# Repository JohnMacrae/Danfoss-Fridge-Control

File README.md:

# Danfoss-Fridge-Control

I have a Danfoss BD35 and BD50 compressor running the fridge and freezer on my boat. This project has been brewing since I sopke with a friend, Rick, back in 2016 but although I tinkered with it, I didn't get serious - mostly due to lack of confidence born out of lack of competence :)
While we were on board in 2019, however, the mechanical thermostat on the fridge (BD35) broke and I was forced to 'create' something out of what was on board  - an ESP8266, a DS18b20 and a chinesium relay.

It was successful and ran for months without any problems but as you can see it was a bit of a bodge.  So, I decided to make a board and run it on an ESP32.

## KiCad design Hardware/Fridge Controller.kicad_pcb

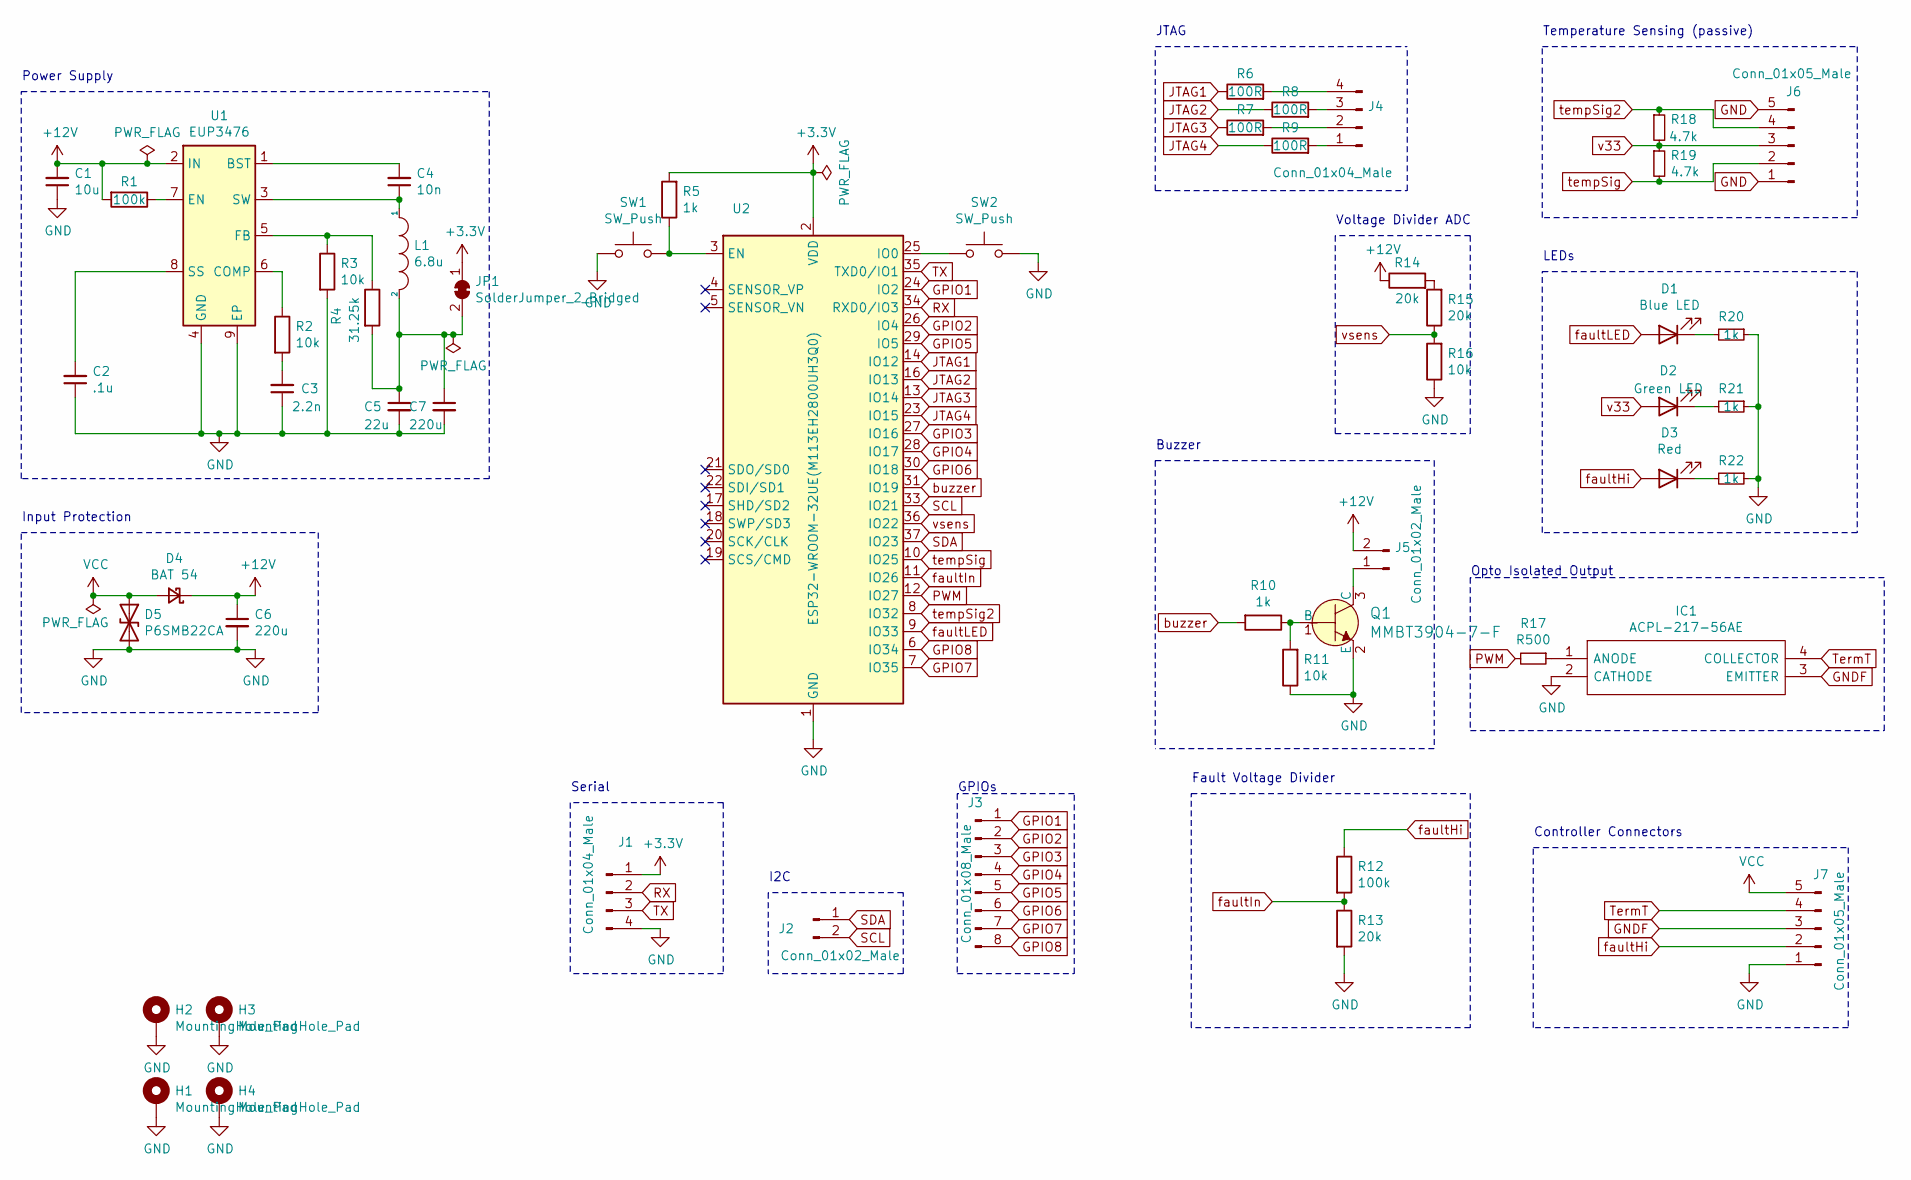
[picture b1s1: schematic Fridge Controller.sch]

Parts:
C1: 10u; C_0805_2012Metric_Pad1.15x1.40mm_HandSolder
C2: .1u; C_0805_2012Metric_Pad1.15x1.40mm_HandSolder
C3: 2.2n; C_0805_2012Metric_Pad1.15x1.40mm_HandSolder
C4: 10n; C_0805_2012Metric_Pad1.15x1.40mm_HandSolder
C5: 22u; C_0805_2012Metric_Pad1.15x1.40mm_HandSolder
C6: 220u; C_1206_3216Metric_Pad1.42x1.75mm_HandSolder
C7: 220u; CP_EIA-7343-31_Kemet-D_Pad2.25x2.55mm_HandSolder
D1: Blue LED; LED_1206_3216Metric
D2: Green LED; LED_1206_3216Metric
D3: Red; LED_1206_3216Metric
D4: BAT 54; D_SOT-23_ANK
D5: P6SMB22CA; D_SMB
H1, H2, H3, H4: MountingHole_Pad; MountingHole_3.2mm_M3_Pad_Via
IC1: ACPL-217-56AE; SOIC127P700X242-4N; Mouser Part Number 630-ACPL-217-56AE
J1, J4: Conn_01x04_Male; PinHeader_1x04_P2.54mm_Vertical
J2, J5: Conn_01x02_Male; PinHeader_1x02_P2.54mm_Vertical
J3: Conn_01x08_Male; PinHeader_1x08_P2.54mm_Vertical
J6, J7: Conn_01x05_Male; JST_XH_B5B-XH-A_1x05_P2.50mm_Vertical
JP1: SolderJumper_2_Bridged; SolderJumper-2_P1.3mm_Open_Pad1.0x1.5mm
L1: 6.8u; L_Abracon_ASPI-0630LR
Q1: MMBT3904-7-F; SOT-23-3; MPN MMBT3904-7-F; Digi-Key_PN MMBT3904-FDICT-ND
R1, R12: 100k; R_0805_2012Metric_Pad1.15x1.40mm_HandSolder
R2, R3, R11, R16: 10k; R_0805_2012Metric_Pad1.15x1.40mm_HandSolder
R4: 31.25k; R_0805_2012Metric_Pad1.15x1.40mm_HandSolder
R5, R10, R20, R21, R22: 1k; R_0805_2012Metric_Pad1.15x1.40mm_HandSolder
R6, R7, R8, R9: 100R; R_0805_2012Metric_Pad1.15x1.40mm_HandSolder
R13, R14, R15: 20k; R_0805_2012Metric_Pad1.15x1.40mm_HandSolder
R17: R500; R_0805_2012Metric_Pad1.15x1.40mm_HandSolder
R18, R19: 4.7k; R_0805_2012Metric_Pad1.15x1.40mm_HandSolder
SW1, SW2: SW_Push; SW_PUSH_6mm_H5mm
U1: EUP3476; HSOP-8-1EP_3.9x4.9mm_P1.27mm_EP2.41x3.1mm
U2: ESP32-WROOM-32UE(M113EH2800UH3Q0); ESP32-WROOM-32

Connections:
+3V3: J1.1, JP1.1 (A), R5.2, U2.2 (VDD)
+12V: C1.2, C6.1, D4.1 (K), J5.2, R1.2, R14.1, U1.2 (IN)
GND: C1.1, C2.1, C3.1, C5.2, C6.2, C7.2, D5.2 (A2), H1.1, H2.1, H3.1, H4.1, IC1.2 (CATHODE), J1.4, J6.1, J6.5, J7.1, Q1.2 (E), R3.2, R11.1, R13.2, R16.1, R20.1, R21.1, R22.1, SW1.1, SW2.2, U1.4 (GND), U1.9 (EP), U2.1 (GND), U2.15 (GND), U2.38 (GND), U2.39 (GND)
GNDF: IC1.3 (EMITTER), J7.3
GPIO1: J3.1, U2.24 (IO2)
GPIO2: J3.2, U2.26 (IO4)
GPIO3: J3.3, U2.27 (IO16)
GPIO4: J3.4, U2.28 (IO17)
GPIO5: J3.5, U2.29 (IO5)
GPIO6: J3.6, U2.30 (IO18)
GPIO7: J3.7, U2.7 (IO35)
GPIO8: J3.8, U2.6 (IO34)
JTAG1: R6.1, U2.14 (IO12)
JTAG2: R8.1, U2.16 (IO13)
JTAG3: R7.1, U2.13 (IO14)
JTAG4: R9.1, U2.23 (IO15)
unnamed: C2.2, U1.8 (SS)
unnamed: C3.2, R2.2
unnamed: C4.1, L1.1, U1.3 (SW)
unnamed: C4.2, U1.1 (BST)
unnamed: C5.1, C7.1, JP1.2 (B), L1.2, R4.2
unnamed: D1.1 (K), R20.2
unnamed: D2.1 (K), R21.2
unnamed: D3.1 (K), R22.2
unnamed: IC1.1 (ANODE), R17.1
unnamed: J4.1, R9.2
unnamed: J4.2, R7.2
unnamed: J4.3, R8.2
unnamed: J4.4, R6.2
unnamed: J5.1, Q1.3 (C)
unnamed: Q1.1 (B), R10.1, R11.2
unnamed: R1.1, U1.7 (EN)
unnamed: R2.1, U1.6 (COMP)
unnamed: R3.1, R4.1, U1.5 (FB)
unnamed: R5.1, SW1.2, U2.3 (EN)
unnamed: R14.2, R15.2
unnamed: SW2.1, U2.25 (IO0)
PWM: R17.2, U2.12 (IO27)
RX: J1.2, U2.34 (RXD0/IO3)
SCL: J2.2, U2.33 (IO21)
SDA: J2.1, U2.37 (IO23)
TX: J1.3, U2.35 (TXD0/IO1)
TermT: IC1.4 (COLLECTOR), J7.4
VCC: D4.2 (A), D5.1 (A1), J7.5
buzzer: R10.2, U2.31 (IO19)
faultHi: D3.2 (A), J7.2, R12.1
faultIn: R12.2, R13.1, U2.11 (IO26)
faultLED: D1.2 (A), U2.9 (IO33)
tempSig: J6.2, R19.2, U2.10 (IO25)
tempSig2: J6.4, R18.1, U2.8 (IO32)
v33: D2.2 (A), J6.3, R18.2, R19.1
vsens: R15.1, R16.2, U2.36 (IO22)

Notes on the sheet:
Temperature Sensing (passive)
LEDs
Opto Isolated Output
JTAG
Power Supply
Controller Connectors
Fault Voltage Divider
Buzzer
Voltage Divider ADC
GPIOs
Serial
I2C
Input Protection

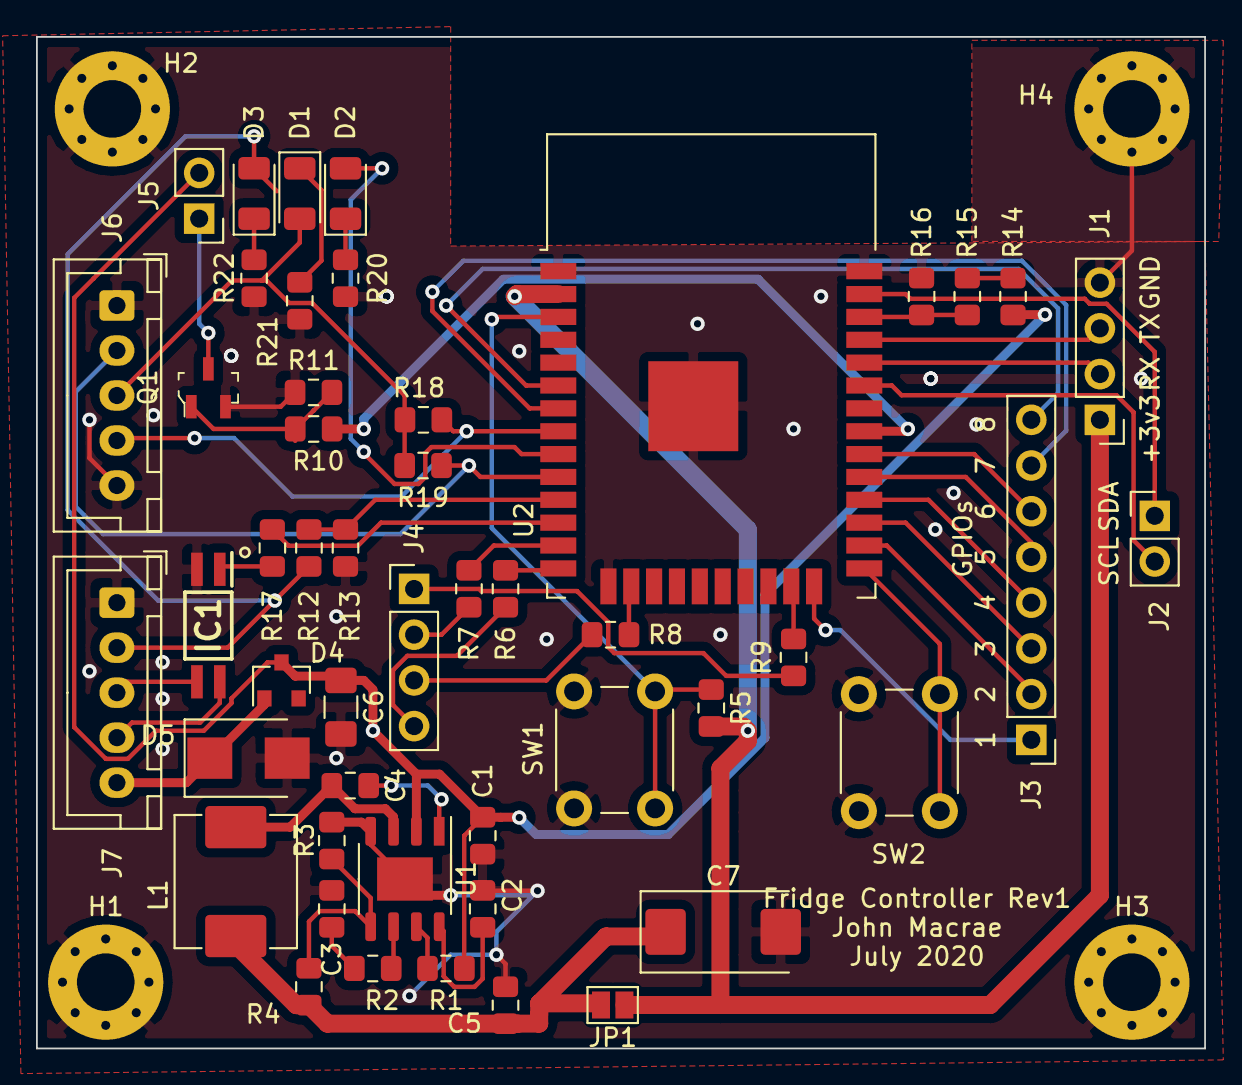
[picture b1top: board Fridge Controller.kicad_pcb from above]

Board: 2 copper layers, 64.9 x 56.2 mm, 53 parts (0 on the bottom side), 52 nets.

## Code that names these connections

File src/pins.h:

#include <Arduino.h>

#define TEMPSIG 21
#define GPIO2 2
#define TX 1
#define RX 3
#define GPIO1 5
#define JTAG1 14
#define JTAG2 16
#define JTAG3 13
#define JTAG4 23
#define GPIO3 16
#define GPIO4 17
#define GPIO5 18
#define GPIO6 19
//#define GPIO7 33 now ow bus
#define VSENS 22
#define SDA 23
#define SCL 25
#define FAULTLED 26
#define FAULTIN 26
#define BUZZER 32
#define PWM 33
#define TEMPSIG2 35

void setPins()
{
    pinMode(FAULTLED, OUTPUT);
    digitalWrite(FAULTLED, LOW);

    pinMode(PWM, OUTPUT);
    digitalWrite(PWM, HIGH);

    pinMode(BUZZER, OUTPUT);
    digitalWrite(BUZZER, LOW);

    pinMode(VSENS, INPUT);
    pinMode(FAULTIN, INPUT);

pinMode(TEMPSIG, OUTPUT);

}

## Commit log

2020-06-29 Initial
2020-06-30 PWM working
2020-07-05 Fixed temperature measurement
2020-08-06 Fixed temperature measurement and buzzer circuit tested
2020-08-06 Up to 6 august
2020-08-10 Added Hardware
2020-08-10 Reorganise
2020-08-10 Reorganise 2
2020-08-10 Reorg 3
2021-08-17 Using OnewireNG
